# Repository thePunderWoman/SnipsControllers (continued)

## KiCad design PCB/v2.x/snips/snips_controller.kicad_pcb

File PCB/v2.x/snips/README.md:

# Snips Controller PCB (V2)

A wireless handheld controller for R2-D2 droid operation, designed for use at public events and conventions. Communicates with the droid over Zigbee, in a packetized state-report architecture.

The electrical design is in [Stackup KDL](stackup/board.kdl), using the pinned
Stackup library. The existing [KiCad PCB](snips_controller.kicad_pcb) is linked
through `snips_controller.stackup_sch`; sync it with the Stackup KiCad plugin. Run
`stackup check PCB/v2.x/snips/stackup/board.kdl` from the repository root before syncing.

A STEP model of the assembled board is in [`step/v2.0/snips_controller.step`](step/v2.0/snips_controller.step).

## V2 board

70 x 30 mm, 4 layers: F.Cu signals, In1 solid 3V3, In2 solid GND, B.Cu signals. 1.6 mm thick. Routed, not yet fabricated.

- **Module:** an ESP32-S3-MINI-1U-N8 on the top, between the macro buttons and USB, turned 270 degrees. The 19.2 mm WROOM-1U does not fit the 17.5 mm there. The turn puts the pinless GND edge on the side and the signal pins toward the stick, the OLED and the carrier; pins are assigned by position, as `GPIO_table.md` explains. USB runs about 15 mm as a result, which is well within full-speed limits. Bluetooth and ESP-NOW work with no other radio.
- **XBee:** optional. U_XBEE1 is a row of 12 hand-solder pads on the bottom for a 22 x 17 mm castellated daughter board, which carries the XBee 3 Micro, its decoupling, the RESET pull-up and RC, and the ATTN/BOOTMODE pull-up. The link is UART with flow control, not SPI. RTS and DTR also allow XBee serial firmware recovery through the ESP32. Leave the area inside the pads free of parts; vias there stay tented. See `GPIO_table.md`.
- **Reflow:** the bottom side goes first and the top side last, because Espressif requires a single reflow for the module (datasheet section 12.3). The XBee reflows on its own carrier and never goes upside down, which is what stopped the two modules from sharing this board before.
- **Radio link:** Amidala's droids use XBee Zigbee 3.0, so a Zigbee controller needs the carrier. The firmware still has to move from the XBee's SPI interface to UART, and needs a V2 pin map.
- **Programming:** USB, through the module's native USB. To force download mode, hold SW_BOOT1 while pressing the power button. RXD0's pull-up holds the latch with no firmware, so a blank board flashes after a 1 s press, with no button held during the upload.
- **No reset button:** the power button turns the board on, and only firmware turns it off. PWR_HOLD is on RXD0, whose pull-up holds the latch through any reset or USB upload, so a blank or hung board stays on until USB and the battery are removed. Keep a watchdog running to recover from a hang. C_LATCH_FB1 gives the latch hysteresis, so that pull-up cannot restart the board at power-off, and R_PWR_EN_PD1 is 22 kΩ so a rising gate cannot couple through it and lift EN.
- **Buttons:** all 13 connect directly to module GPIOs. See `GPIO_table.md`.
- **Power blocks:** the buck, charger and power latch follow V1's relative placement, all on the bottom. Two charger GND vias were moved 0.1-0.75 mm in V1's layout to clear earlier button positions. C_BUCK_IN1 turned 90 degrees with its VSYS pad straight above the VIN pin. BUCK_FB runs around the input cap and hops to F.Cu past the inductor, so both planes shield it; keep it out from under L_BUCK1. The latch is too long to fit whole, so it is split at `PWR_BTN_TRIGGER`: the switch and `PWR_LATCH_G` node sit under the stick, turned 270 degrees, and the inverter sits beside the stick's lower pins. See `diagrams/` for why they are arranged this way.
- **OLED cable:** U_OLED1's opening faces USB, and a Qwiic plug is 7.0 mm wide with its protrusions, so keep top-side parts out of x 0.9-7.9 mm from the mouth at y 52.7 mm down to the MH3 post. Check that a real cable goes in before committing the shell.
- **BOM:** the Value column carries each part's full details, including a capacitor's rated voltage, because fabs read it and the BOM has no voltage column. Keep rail names out of designators: PCBWay queried the V1.2 caps named C_3V3_* as 3.3 V parts, so V2 uses C_MCU_*.
- **Hall sensor:** U_HALL1 is on the bottom at (6.5, 4.75) mm, rotated 180 degrees, forward and left of the stick, 7.8 mm from its nearest pot pin in plan view against about 15.4 mm on V1. A 2 x 2 mm N52 magnet swings up to sit directly under the package centre. Keep at least 1.8 mm from the top of the package to the magnet at full press, or the output clips at the sensor's ±44 mT range. The stick reading against trigger travel still needs a bench test.
- **Mounting:** four Ø2.2 mm unplated holes, MH1-4, at (2.5, 2.6), (27.4, 2.8), (3, 62.5) and (27, 67) from the top-left corner, for M2 self-tapping screws into shell posts. MH3 sits above the power button, which holds the true corner, so a Ø4 post clears `C_DBNC1` by only about 0.15 mm. The carrier has a long shallow chamfer at that corner, which also clears a Ø4 post on the bottom.
- **Battery:** BT1 is a 2-pin JST PH, the common connector on pouch cells this size: pin 1 VBAT, pin 2 GND. R_TS1 ties the charger's TS pin to a fixed 10 kΩ, so there is no pack temperature monitoring. Check the polarity of the cell's lead before plugging it in.
- **USB and status LED:** J_USB1 sits 2 mm right of centre, with its CC resistors and TVS moved with it. D_RGB1 sits between SW_PWR1 and J_USB1, turned 90 degrees.
- **Through-board parts:** the Alps pegs, stick pins, USB stakes and BT1 pins all reach the other side.

## GPIO Assignment

See [`GPIO_table.md`](GPIO_table.md) for every module pin.

## Hardware Overview

| Component | Part | Notes | Layout diagram |
|---|---|---|---|
| MCU and radio | Espressif ESP32-S3-MINI-1U-N8 | Wi-Fi, Bluetooth LE and ESP-NOW, 8 MB flash, 15.4 x 15.4 x 2.4 mm, external antenna | — |
| XBee (optional) | Digi XB3-24Z8UM on a castellated carrier | Zigbee 3.0, +19 dBm, U.FL. Hand-soldered to the underside | — |
| Display | SSD1306 1.3" OLED | 128x64, monochrome, I2C | — |
| Hall trigger | DRV5055A2QDBZR (SOT-23) | Ratiometric linear hall effect, 3.3V. On the bottom of the board under the trigger magnet; senses the field perpendicular to the board. Trigger calibration accepts either magnet polarity | — |
| Thumbstick | GuliKit hall effect module | Native 3.3V, analog X/Y + click | — |
| Macro and boot buttons | Alps SKRPABE010 | 4.2 x 3.2 x 2.5 mm SMD tact switch, 1.57 N, 0.2 mm travel, 100,000 cycles. Footprint checked against the Alps land drawing | — |
| RGB LED | SK6812MINI-HS | Status indicator; specified supply begins at 3.7 V, but board supplies 3.3 V | — |
| Charger | bq25185 | USB/DC input, power path, 4.2V/500mA | [diagram](diagrams/power_charger_layout.md) |
| Buck | TLV62569 | 3.3V output, 2A | [diagram](diagrams/power_buck_layout.md) |
| Battery | Single-cell pouch, 2-pin JST PH | Cell not chosen yet. Set R_ISET1 for it; 604 Ω charges at about 500 mA | — |
| Power switch | AO3401A + AO3400A | Soft latch, hybrid hardware+firmware | [diagram](diagrams/power_control_layout.md) |

## Layout Diagrams

Suggested top-copper floorplans for the three sheets with real layout
stakes — a switching regulator, a linear charger with a thermal pad, and
the soft latch that switches the buck's enable. Each is checked
against the actual component datasheet, not just the schematic. See
[`diagrams/README.md`](diagrams/README.md) for the full list and how the
files are organized.

- [Buck converter](diagrams/power_buck_layout.md) — `/Power_Buck/*` nets in Stackup
- [Charger](diagrams/power_charger_layout.md) — `/Power_Charger/*` nets in Stackup
- [Power latch](diagrams/power_control_layout.md) — `/Power_Control/*` nets in Stackup

## Passives & Support Components

### Decoupling Caps
| Component | Value | Notes |
|---|---|---|
| DRV5055 VCC | 100nF ceramic | |
| GuliKit VCC | 100nF ceramic | |
| SK6812 VCC | 100nF ceramic | Close to supply pin |
| ICM-42670-P | 100nF + 2.2µF on VDD, 10nF on VDDIO | Close to their pins |
| OLED connector | 1µF + 100nF ceramic | |
| bq25185 VIN | 10µF + 100nF ceramic | |
| bq25185 SYS | 10µF + 100nF ceramic | |
| bq25185 BAT | 10µF ceramic | |
| TLV62569 VIN | 10µF ceramic | |
| TLV62569 VOUT | 22µF ceramic | As on V1. TI specifies 10-47 µF |
| ESP32-S3-MINI-1U 3V3 | 10µF + 100nF + 39pF ceramic | As on V1 |
| ESP32-S3-MINI-1U EN | 1µF ceramic | With R_EN_PU1, per Espressif |
| XBee VCC | 10µF + 1µF + 47pF ceramic | On the carrier, per Digi 90001543 p.52 |

### Resistors
| Signal | Value | Notes |
|---|---|---|
| bq25185 STAT1/STAT2 | 10kΩ | Open drain, pulled up to 3V3 |
| bq25185 TS/MR | 10kΩ to GND | Required with no thermistor: floating means no charging |
| I2C SDA/SCL | 4.7kΩ | So the IMU works with no OLED attached |
| Boot button | 10kΩ to 3V3 | R_BOOT_PU1 |
| ESP32 EN | 10kΩ to 3V3 | R_EN_PU1 |
| USB D+/D- | 27Ω series | R_USB_DP1 and R_USB_DM1, as on V1 |
| Trigger output | 1kΩ + 100nF | R_TRIG1 and C_TRIG1, about 1.6 kHz. The DRV5055 must not see a capacitor without a resistor |
| SK6812 DIN | 470Ω | R_RGB1 |

### Buttons
No external parts. Every button wires to GND and a module GPIO, using the internal pull-ups; see [`GPIO_table.md`](GPIO_table.md).

---

## Communication Architecture

The droids use XBee Zigbee 3.0, so the controller joins that network through the XBee on the carrier, over UART in API mode. Each droid has its own coordinator and PAN ID, and all coordinators share one AES key. Without the carrier the ESP32 can use Bluetooth or ESP-NOW.

---

## Bringup Sequence

Recommended bringup order:
1. Current-limited supply on VSYS, with no carrier fitted: press power for 1 s, then check 3V3 and idle current.
2. Flash over USB with no button held, with SW_BOOT1 held at power-on if the chip does not enumerate. Confirm `PWR_HOLD` reads high.
3. Time the shortest press that stays on, at 3.3 V and 4.2 V. The simulation gives under 0.4 s at worst, so a 1 s press is well clear. Run a USB upload with no button held, then confirm a watchdog reset reboots the board. Power off at least 20 times, on USB and on battery, and scope `PWR_EN` and `PWR_LATCH_G`: the board must stay off every time, since the simulation's margin has not been measured.
4. OLED and ICM-42670-P on I2C.
5. SK6812 RGB LED.
6. Buttons, using the pin table.
7. Charge status on STAT1 and STAT2, and VSYS sense.
8. DRV5055 and thumbstick on the ADC. Sweep the stick and the trigger together to measure how much each moves the other.
9. Solder the carrier on. Check UART traffic, CTS, SLEEP_RQ and ON/SLEEP, then XBee reset, then join a droid's network.

---

## Power Architecture

- Battery → bq25185 (charger and power path, 4.2V, 500mA) → TLV62569 (3.3V buck) → 3V3 for everything, including the carrier.
- Power switch: soft latch (AO3401A PFET + AO3400A NFET) controls the TLV62569 EN pin. USB does not hold it on.
- Boot: press the power button for about a second → latch enables 3V3 → RXD0's pull-up holds the latch through D_OR2 as soon as the chip has power → firmware drives RXD0 high.
- Shutdown: firmware sees a hold on IO21 → graceful shutdown → RXD0 low → the gate decays through R_LATCH_G1 → C_LATCH_FB1 kicks it clear of threshold as PWR_EN falls → power cut after about 0.8-2.6 s, counted from release if the button is still held.
- bq25185 STAT1 and STAT2 go to IO15 and IO14 (open drain, 10kΩ pull-ups to 3V3).
- Battery voltage: VSYS through R_VSYS1/R_VSYS2 to IO7, reading VSYS/3.
- Below about 3.3 V on the battery the buck passes it through, and the DRV5055's minimum is 3.0 V, so the firmware cutoff should sit above that.

## Power Management

Firmware implements tiered power saving:
- **Active**: full brightness OLED, normal polling rate
- **Idle (short timeout)**: OLED dimmed via SSD1306 contrast command
- **Idle (long timeout)**: OLED off
- **Sleep**: MCU sleep, wake on any button press via GPIO interrupt

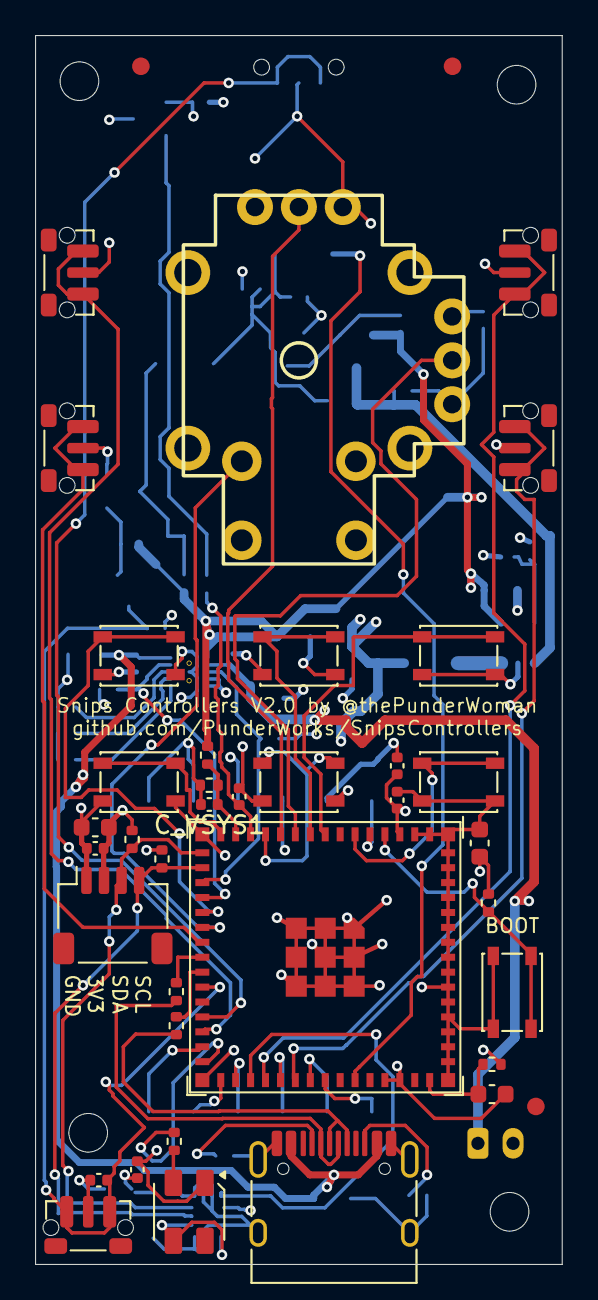
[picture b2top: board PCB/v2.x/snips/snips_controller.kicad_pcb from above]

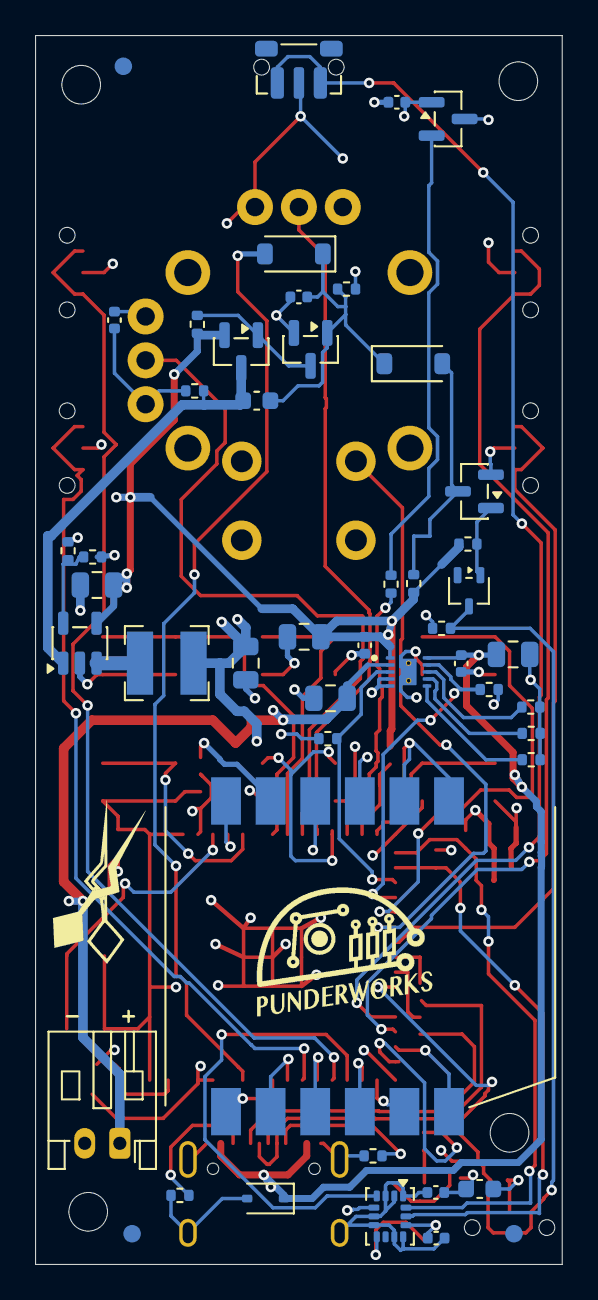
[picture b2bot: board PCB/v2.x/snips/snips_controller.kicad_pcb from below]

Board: 4 copper layers, 30.0 x 70.0 mm, 93 parts (50 on the bottom side), 56 nets.

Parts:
BT1: JST PH 2-pin 2mm | S2B-PH-K(LF)(SN) | JST | Throu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; JST_PH_S2B-PH-K_1x02_P2.00mm_Horizontal
C_BAT1: 10µF 25V X5R ±10% | CL21A106KAYNNNE | Samsung | 0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; C_0805_2012Metric
C_BUCK_IN1: 10µF 25V X5R ±10% | CL21A106KAYNNNE | Samsung | 0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; C_0805_2012Metric
C_BUCK_OUT1: 22µF 25V X5R ±20% | CL21A226MAQNNNE | Samsung | 0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; C_0805_2012Metric
C_DBNC1: 100nF 16V X7R ±10% | CL05B104KO5NNNC | Samsung | 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; C_0402_1005Metric
C_EN1: 1µF 50V X5R ±10% | CL10A105KB8NNNC | Samsung | 06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; C_0603_1608Metric
C_HALL1: 100nF 16V X7R ±10% | CL05B104KO5NNNC | Samsung | 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; C_0402_1005Metric
C_IMU_1: 100nF 16V X7R ±10% | CL05B104KO5NNNC | Samsung | 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; C_0402_1005Metric
C_IMU_2: 2.2µF 10V X7R ±10% | CL10B225KP8NNNC | Samsung | 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; C_0603_1608Metric
C_IMU_3: 10nF 50V X7R ±10% | CL05B103KB5NNNC | Samsung | 0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; C_0402_1005Metric
C_LATCH_FB1: 1µF 50V X5R ±10% | CL10A105KB8NNNC | Samsung | 06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; C_0603_1608Metric
C_LATCH_G1: 1µF 6.3V X5R ±10% | CL05A105KQ5NNNC | Samsung | 0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; C_0402_1005Metric
C_MCU_1: 10µF 10V X5R ±10% | CL10A106KP8NNNC | Samsung | 0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; C_0603_1608Metric
C_MCU_2: 100nF 16V X7R ±10% | CL05B104KO5NNNC | Samsung | 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; C_0402_1005Metric
C_MCU_3: 39pF 50V NP0 ±5% | CC0402JRNPO9BN390 | Yageo | 04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; C_0402_1005Metric
C_OLED_1: 1µF 50V X5R ±10% | CL10A105KB8NNNC | Samsung | 06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; C_0603_1608Metric
C_OLED_2: 100nF 16V X7R ±10% | CL05B104KO5NNNC | Samsung | 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; C_0402_1005Metric
C_RGB1: 100nF 16V X7R ±10% | CL05B104KO5NNNC | Samsung | 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; C_0402_1005Metric
C_STICK1: 100nF 16V X7R ±10% | CL05B104KO5NNNC | Samsung | 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; C_0402_1005Metric
C_SYS_1: 10µF 25V X5R ±10% | CL21A106KAYNNNE | Samsung | 0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; C_0805_2012Metric
C_SYS_2: 100nF 16V X7R ±10% | CL05B104KO5NNNC | Samsung | 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; C_0402_1005Metric
C_TRIG1: 100nF 16V X7R ±10% | CL05B104KO5NNNC | Samsung | 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; C_0402_1005Metric
C_VIN_1: 10µF 25V X5R ±10% | CL21A106KAYNNNE | Samsung | 0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; C_0805_2012Metric
C_VIN_2: 100nF 16V X7R ±10% | CL05B104KO5NNNC | Samsung | 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; C_0402_1005Metric
C_VSYS1: 100nF 16V X7R ±10% | CL05B104KO5NNNC | Samsung | 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; C_0402_1005Metric
D_INV_ISO1: Schottky diode 30V 200mA | BAT54W-7-F | Diodes In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; SOT-323_SC-70
D_OR1, D_OR2: 1N4148W switching diode 75V 150mA | 1N4148W | ST 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; D_SOD-123
D_RGB1: Addressable RGB LED | SK6812MINI-HS | OPSCO | 3.5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; SK6812MINI-HS-012
D_VBUS_TVS1: TVS diode 5V bidirectional | TPPESD5V0S1BA | TECH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; D_SOD-323
FID1, FID2, FID3, FID4, FID5, FID6: Fiducial_1mm_Mask2mm
J_STICK1: Hall thumbstick | GuliKit_Thumbstick | GuliKit | 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; GuliKit_HallStick
J_USB1: USB-C receptacle 16-pin | TYPE-C-31-M-12 | Hropar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; USB_C_Receptacle_HRO_TYPE-C-31-M-12
LOGO2: LOGO
LOGO4: PunderWorks_Logo_10mm
L_BUCK1: 2.2µH ±20% 2.9A 44mΩ power inductor | SRN4018-2R2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; L_Bourns-SRN4018
MH1, MH2, MH3, MH4: MountingHole_2.2mm_M2_ISO14580
Q_INV1: NPN transistor 40V 200mA hFE 100-300 | MMBT3904(R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; SOT-23
Q_LATCH1: N-channel MOSFET 30V 5.7A | AO3400A | AOS | SOT-23; SOT-23
Q_PWR1: P-channel MOSFET 30V 4A | AO3401A | AOS | SOT-23; SOT-23
R_BOOT_PU1: 10kΩ ±1% 62.5mW | 0402WGF1002TCE | UNI-ROYAL | 04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; R_0402_1005Metric
R_BTN_PU1: 100kΩ ±1% 62.5mW | 0402WGF1003TCE | UNI-ROYAL | 0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; R_0402_1005Metric
R_CC1, R_CC2: 5.1kΩ ±1% 62.5mW | 0402WGF5101TCE | UNI-ROYAL | 0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; R_0402_1005Metric
R_EN_PU1: 10kΩ ±1% 62.5mW | 0402WGF1002TCE | UNI-ROYAL | 04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; R_0402_1005Metric
R_FB1: 255kΩ ±1% 62.5mW | RC0402FR-07255KL | Yageo | 0402; R_0402_1005Metric
R_FB2: 56.2kΩ ±1% 62.5mW | RC0402FR-0756K2L | Yageo | 04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; R_0402_1005Metric
R_GATE1: 100kΩ ±1% 62.5mW | 0402WGF1003TCE | UNI-ROYAL | 0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; R_0402_1005Metric
R_I2C_SCL1, R_I2C_SDA1: 4.7kΩ ±1% 62.5mW | 0402WGF4701TCE | UNI-ROYAL | 0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; R_0402_1005Metric
R_INV_BASE1: 220kΩ ±1% 62.5mW | 0402WGF2203TCE | UNI-ROYAL | 0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; R_0402_1005Metric
R_INV_PU1: 220kΩ ±1% 62.5mW | 0402WGF2203TCE | UNI-ROYAL | 0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; R_0402_1005Metric
R_ISET1: 604Ω ±1% 62.5mW | AC0402FR-07604RL | Yageo | 0402; R_0402_1005Metric
R_LATCH_G1: 1MΩ ±1% 62.5mW | 0402WGF1004TCE | UNI-ROYAL | 0402; R_0402_1005Metric
R_PWR_EN_PD1: 22kΩ ±1% 62.5mW | 0402WGF2202TCE | UNI-ROYAL | 04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; R_0402_1005Metric
R_RGB1: 470Ω ±1% 62.5mW | 0402WGF4700TCE | UNI-ROYAL | 04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; R_0402_1005Metric
R_STAT1, R_STAT2: 10kΩ ±1% 62.5mW | 0402WGF1002TCE | UNI-ROYAL | 04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; R_0402_1005Metric
R_TRIG1: 1kΩ ±1% 62.5mW | 0402WGF1001TCE | UNI-ROYAL | 0402; R_0402_1005Metric
R_TS1: 10kΩ ±1% 62.5mW | 0402WGF1002TCE | UNI-ROYAL | 04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; R_0402_1005Metric
R_USB_DM1: 27Ω ±1% 62.5mW | RC0402FR-0727RL | Yageo | 0402; R_0402_1005Metric
R_USB_DP1: 27Ω ±1% 62.5mW | RC0402FR-0727RL | Yageo | 0402; R_0402_1005Metric
R_VSET1: 18kΩ ±1% 62.5mW | RC0402FR-0718KL | Yageo | 0402; R_0402_1005Metric
R_VSYS1: 200kΩ ±1% 62.5mW | 0402WGF2003TCE | UNI-ROYAL | 0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; R_0402_1005Metric
R_VSYS2: 100kΩ ±1% 62.5mW | 0402WGF1003TCE | UNI-ROYAL | 0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; R_0402_1005Metric
SW_BOOT1: Tact switch 1.6N 100k cycles | SKRPABE010 | Alps 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; SW_Alps_SKRP
SW_MACRO1, SW_MACRO2, SW_MACRO3, SW_MACRO4, SW_MACRO5, SW_MACRO6: Tact switch 1.6N 100k cycles | SKRPABE010 | Alps 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; SW_Alps_SKRP
SW_PWR1: Side-push tact switch 1.6N 100k cycles | SKRTLAE0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; SW_Push_1P1T-MP_NO_Horizontal_Alps_SKRTLAE010
SW_THR_DN1: Side-push tact switch 1.6N 100k cycles | SKRTLAE0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; SW_Push_1P1T-MP_NO_Horizontal_Alps_SKRTLAE010
SW_THR_UP1: Side-push tact switch 1.6N 100k cycles | SKRTLAE0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; SW_Push_1P1T-MP_NO_Horizontal_Alps_SKRTLAE010
SW_TRIG_DIG1: Side-push tact switch 1.6N 100k cycles | SKRTLAE0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; SW_Push_1P1T-MP_NO_Horizontal_Alps_SKRTLAE010
SW_VOL_DN1: Side-push tact switch 1.6N 100k cycles | SKRTLAE0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; SW_Push_1P1T-MP_NO_Horizontal_Alps_SKRTLAE010
SW_VOL_UP1: Side-push tact switch 1.6N 100k cycles | SKRTLAE0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; SW_Push_1P1T-MP_NO_Horizontal_Alps_SKRTLAE010
U_BUCK1: Adjustable buck converter 2A | TLV62569DBVR | TI 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; SOT-23-5
U_CHG1: 1-cell Li-ion charger 1A | BQ25185DLHR | TI | WSO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; IC_BQ25185DLHR
U_HALL1: Linear hall sensor A2 ±42mT | DRV5055A2QDBZR | TI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; SOT-23
U_IMU1: 6-axis IMU | ICM-42670-P | TDK InvenSense | LGA-1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; LGA-14_3x2.5mm_P0.5mm_LayoutBorder3x4y
U_MCU1: Wi-Fi BLE module 8MB flash no PSRAM | ESP32-S3-MI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; ESP32-S3-MINI-1U
U_OLED1: JST SH 4-pin 1mm Qwiic | SM04B-SRSS-TB(LF)(SN) | 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; JST_SH_SM04B-SRSS-TB_1x04-1MP_P1.00mm_Horizontal
U_XBEE1: XBee carrier pads no part | Snips XBee carrier | 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; XBee_Carrier_Castellated

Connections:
3V3: C_BUCK_OUT1.1, C_HALL1.1, C_IMU_1.1, C_IMU_2.1, C_IMU_3.1, C_MCU_1.1, C_MCU_2.1, C_MCU_3.1, C_OLED_1.1, C_OLED_2.1, C_RGB1.1, C_STICK1.1, D_RGB1.3, J_STICK1.3 (X_HI), J_STICK1.3' (Y_HI), L_BUCK1.2, R_BOOT_PU1.2, R_BTN_PU1.1, R_EN_PU1.2, R_FB1.2, R_I2C_SCL1.1, R_I2C_SDA1.1, R_STAT1.2, R_STAT2.2, U_HALL1.1, U_IMU1.5, U_IMU1.8, U_IMU1.12, U_MCU1.3, U_OLED1.2 (VCC), U_XBEE1.9, U_XBEE1.10
/Accelerometer/I2C_SCL: R_I2C_SCL1.2, U_IMU1.13, U_MCU1.17, U_OLED1.4 (SCL)
/Accelerometer/I2C_SDA: R_I2C_SDA1.2, U_IMU1.14, U_MCU1.16, U_OLED1.3 (SDA)
/Buttons_Direct/BTN_MACRO1: SW_MACRO1.1, U_MCU1.20
/Buttons_Direct/BTN_MACRO2: SW_MACRO2.1, U_MCU1.9
/Buttons_Direct/BTN_MACRO3: SW_MACRO3.1, U_MCU1.8
/Buttons_Direct/BTN_MACRO4: SW_MACRO4.1, U_MCU1.15
/Buttons_Direct/BTN_MACRO5: SW_MACRO5.1, U_MCU1.12
/Buttons_Direct/BTN_MACRO6: SW_MACRO6.1, U_MCU1.6
/Buttons_Direct/BTN_THR_DN: SW_THR_DN1.1, U_MCU1.22
/Buttons_Direct/BTN_THR_UP: SW_THR_UP1.1, U_MCU1.28
/Buttons_Direct/BTN_TRIG_DIG: SW_TRIG_DIG1.1, U_MCU1.27
/Buttons_Direct/BTN_VOL_DN: SW_VOL_DN1.1, U_MCU1.36
/Buttons_Direct/BTN_VOL_UP: SW_VOL_UP1.1, U_MCU1.34
/Hall_Trigger/TRIG_ADC: C_TRIG1.1, R_TRIG1.2, U_MCU1.13
/Hall_Trigger/TRIG_ANALOG: R_TRIG1.1, U_HALL1.2
/MCU_Core/BTN_STICK: J_STICK1.a (SW_A), U_MCU1.21
/MCU_Core/MCU_BOOT: R_BOOT_PU1.1, SW_BOOT1.2, U_MCU1.4
/MCU_Core/MCU_EN: C_EN1.1, R_EN_PU1.1, U_MCU1.45
/MCU_Core/PWR_BTN_SENSE: C_DBNC1.1, D_INV_ISO1.3 (K), R_BTN_PU1.2, SW_PWR1.1, U_MCU1.25
/MCU_Core/PWR_HOLD: D_OR2.2 (A), U_MCU1.40
/MCU_Core/RGB_DIN: R_RGB1.2, U_MCU1.30
/MCU_Core/STAT1: R_STAT1.1, U_CHG1.9 (STAT1), U_MCU1.19
/MCU_Core/STAT2: R_STAT2.1, U_CHG1.3 (STAT2), U_MCU1.18
/MCU_Core/STICK_X: J_STICK1.2 (X_OUT), U_MCU1.11
/MCU_Core/STICK_Y: J_STICK1.2' (Y_OUT), U_MCU1.10
/MCU_Core/USB_DM: J_USB1.A7 (D-), J_USB1.B7 (D-), R_USB_DM1.1
/MCU_Core/USB_DM_MCU: R_USB_DM1.2, U_MCU1.23
/MCU_Core/USB_DP: J_USB1.A6 (D+), J_USB1.B6 (D+), R_USB_DP1.1
/MCU_Core/USB_DP_MCU: R_USB_DP1.2, U_MCU1.24
/MCU_Core/VSYS_SENSE: C_VSYS1.1, R_VSYS1.2, R_VSYS2.1, U_MCU1.14
/Power_Buck/BUCK_FB: R_FB1.1, R_FB2.1, U_BUCK1.5 (FB)
/Power_Buck/BUCK_SW: L_BUCK1.1, U_BUCK1.3 (SW)
/Power_Buck/PWR_EN: C_LATCH_FB1.1, Q_PWR1.3 (D), R_PWR_EN_PD1.1, U_BUCK1.1 (EN)
/Power_Charger/CHG_ISET: R_ISET1.1, U_CHG1.8 (ISET)
/Power_Charger/CHG_TS: R_TS1.1, U_CHG1.6 (TS/MR)
/Power_Charger/CHG_VSET: R_VSET1.1, U_CHG1.7 (ILIM/VSET)
/Power_Control/PWR_BTN_INV_BASE: D_INV_ISO1.1 (A), Q_INV1.1 (B), R_INV_BASE1.2
/Power_Control/PWR_BTN_TRIGGER: D_OR1.2 (A), Q_INV1.3 (C), R_INV_PU1.2
/Power_Control/PWR_GATE: Q_LATCH1.3 (D), Q_PWR1.1 (G), R_GATE1.2
/Power_Control/PWR_LATCH_G: C_LATCH_FB1.2, C_LATCH_G1.2, D_OR1.1 (K), D_OR2.1 (K), Q_LATCH1.1 (G), R_LATCH_G1.2
/RGB_LED/RGB_DIN_R: D_RGB1.2, R_RGB1.1
/USB_C/USB_CC1: J_USB1.A5 (CC1), R_CC1.1
/USB_C/USB_CC2: J_USB1.B5 (CC2), R_CC2.1
/XBee/XBEE_CTS: U_MCU1.29, U_XBEE1.1
/XBee/XBEE_DIN: U_MCU1.31, U_XBEE1.2
/XBee/XBEE_DOUT: U_MCU1.32, U_XBEE1.3
/XBee/XBEE_ON_SLEEP: U_MCU1.37, U_XBEE1.5
/XBee/XBEE_RESET: U_MCU1.38, U_XBEE1.6
/XBee/XBEE_RTS: U_MCU1.35, U_XBEE1.4
/XBee/XBEE_SLEEP_RQ: U_MCU1.5, U_XBEE1.7
ACCEL_INT1: U_IMU1.4, U_MCU1.33
GND: BT1.2, C_BAT1.2, C_BUCK_IN1.2, C_BUCK_OUT1.2, C_DBNC1.2, C_EN1.2, C_HALL1.2, C_IMU_1.2, C_IMU_2.2, C_IMU_3.2, C_LATCH_G1.1, C_MCU_1.2, C_MCU_2.2, C_MCU_3.2, C_OLED_1.2, C_OLED_2.2, C_RGB1.2, C_STICK1.2, C_SYS_1.2, C_SYS_2.2, C_TRIG1.2, C_VIN_1.2, C_VIN_2.2, C_VSYS1.2, D_RGB1.1, D_VBUS_TVS1.2 (A2), J_STICK1.1 (X_LO), J_STICK1.1' (Y_LO), J_STICK1.c (SW_C), J_USB1.A1 (GND), J_USB1.A12 (GND), J_USB1.B1 (GND), J_USB1.B12 (GND), J_USB1.SH (SHIELD), Q_INV1.2 (E), Q_LATCH1.2 (S), R_CC1.2, R_CC2.2, R_FB2.2, R_ISET1.2, R_LATCH_G1.1, R_PWR_EN_PD1.2, R_TS1.2, R_VSET1.2, R_VSYS2.2, SW_BOOT1.1, SW_MACRO1.2, SW_MACRO2.2, SW_MACRO3.2, SW_MACRO4.2, SW_MACRO5.2, SW_MACRO6.2, SW_PWR1.2, SW_THR_DN1.2, SW_THR_UP1.2, SW_TRIG_DIG1.2, SW_VOL_DN1.2, SW_VOL_UP1.2, U_BUCK1.2 (GND), U_CHG1.4 (~CE), U_CHG1.5 (GND), U_CHG1.11 (THERMAL_PAD), U_CHG1.12, U_CHG1.13, U_HALL1.3, U_IMU1.1, U_IMU1.2, U_IMU1.3, U_IMU1.6, U_IMU1.7, U_IMU1.10, U_IMU1.11, U_MCU1.1, U_MCU1.2, U_MCU1.42, U_MCU1.43, U_MCU1.46, U_MCU1.47, U_MCU1.48, U_MCU1.49, U_MCU1.50, U_MCU1.51, U_MCU1.52, U_MCU1.53, U_MCU1.54, U_MCU1.55, U_MCU1.56, U_MCU1.57, U_MCU1.58, U_MCU1.59, U_MCU1.60, U_MCU1.61, U_MCU1.62, U_MCU1.63, U_MCU1.64, U_MCU1.65, U_OLED1.1 (GND), U_XBEE1.8, U_XBEE1.11, U_XBEE1.12
VBAT: BT1.1, C_BAT1.1, U_CHG1.2 (BAT)
VBUS: C_VIN_1.1, C_VIN_2.1, D_VBUS_TVS1.1 (A1), J_USB1.A4 (VBUS), J_USB1.A9 (VBUS), J_USB1.B4 (VBUS), J_USB1.B9 (VBUS), U_CHG1.10 (IN)
VSYS: C_BUCK_IN1.1, C_SYS_1.1, C_SYS_2.1, Q_PWR1.2 (S), R_GATE1.1, R_INV_BASE1.1, R_INV_PU1.1, R_VSYS1.1, U_BUCK1.4 (VIN), U_CHG1.1 (SYS)

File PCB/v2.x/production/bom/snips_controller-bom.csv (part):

Refs,Quantity,Value,Footprint,MF,MPN,LCSC,Mouser,DigiKey,Hand,DNP
"U_CHG1","1","1-cell Li-ion charger 1A | BQ25185DLHR | TI | WSON-10","BQ25185DLHR:IC_BQ25185DLHR","Texas Instruments","BQ25185DLHR","C19725033","","","",""
"R_BTN_PU1,R_GATE1,R_VSYS2","3","100kΩ ±1% 62.5mW | 0402WGF1003TCE | UNI-ROYAL | 0402","Resistor_SMD:R_0402_1005Metric","UNI-ROYAL(Uniroyal Elec)","0402WGF1003TCE","C25741","","","",""
"C_DBNC1,C_HALL1,C_IMU_1,C_MCU_2,C_OLED_2,C_RGB1,C_STICK1,C_SYS_2,C_TRIG1,C_VIN_2,C_VSYS1","11","100nF 16V X7R ±10% | CL05B104KO5NNNC | Samsung | 0402","Capacitor_SMD:C_0402_1005Metric","Samsung Electro-Mechanics","CL05B104KO5NNNC","C1525","","","",""
"R_BOOT_PU1,R_EN_PU1,R_STAT1,R_STAT2,R_TS1","5","10kΩ ±1% 62.5mW | 0402WGF1002TCE | UNI-ROYAL | 0402","Resistor_SMD:R_0402_1005Metric","UNI-ROYAL(Uniroyal Elec)","0402WGF1002TCE","C25744","","","",""
"C_IMU_3","1","10nF 50V X7R ±10% | CL05B103KB5NNNC | Samsung | 0402","Capacitor_SMD:C_0402_1005Metric","Samsung Electro-Mechanics","CL05B103KB5NNNC","C15195","","","",""
"C_MCU_1","1","10µF 10V X5R ±10% | CL10A106KP8NNNC | Samsung | 0603","Capacitor_SMD:C_0603_1608Metric","Samsung Electro-Mechanics","CL10A106KP8NNNC","C19702","","","",""
"C_BAT1,C_BUCK_IN1,C_SYS_1,C_VIN_1","4","10µF 25V X5R ±10% | CL21A106KAYNNNE | Samsung | 0805","Capacitor_SMD:C_0805_2012Metric","Samsung Electro-Mechanics","CL21A106KAYNNNE","C15850","","","",""
"R_VSET1","1","18kΩ ±1% 62.5mW | RC0402FR-0718KL | Yageo | 0402","Resistor_SMD:R_0402_1005Metric","Yageo","RC0402FR-0718KL","C138044","","","",""
"R_LATCH_G1","1","1MΩ ±1% 62.5mW | 0402WGF1004TCE | UNI-ROYAL | 0402","Resistor_SMD:R_0402_1005Metric","UNI-ROYAL(Uniroyal Elec)","0402WGF1004TCE","C26083","","","",""
"D_OR1,D_OR2","2","1N4148W switching diode 75V 150mA | 1N4148W | ST | SOD-123","Diode_SMD:D_SOD-123","ST(Semtech)","1N4148W","C81598","","","",""
"R_TRIG1","1","1kΩ ±1% 62.5mW | 0402WGF1001TCE | UNI-ROYAL | 0402","Resistor_SMD:R_0402_1005Metric","UNI-ROYAL(Uniroyal Elec)","0402WGF1001TCE","C11702","","","",""
"C_EN1,C_LATCH_FB1,C_OLED_1","3","1µF 50V X5R ±10% | CL10A105KB8NNNC | Samsung | 0603","Capacitor_SMD:C_0603_1608Metric","Samsung Electro-Mechanics","CL10A105KB8NNNC","C15849","","","",""
"C_LATCH_G1","1","1µF 6.3V X5R ±10% | CL05A105KQ5NNNC | Samsung | 0402","Capacitor_SMD:C_0402_1005Metric","Samsung Electro-Mechanics","CL05A105KQ5NNNC","C107372","","","",""
"C_IMU_2","1","2.2µF 10V X7R ±10% | CL10B225KP8NNNC | Samsung | 0603","Capacitor_SMD:C_0603_1608Metric","Samsung Electro-Mechanics","CL10B225KP8NNNC","C100082","","","",""
"L_BUCK1","1","2.2µH ±20% 2.9A 44mΩ power inductor | SRN4018-2R2M | Bourns | SMD 4x4mm","Inductor_SMD:L_Bourns-SRN4018","Bourns","SRN4018-2R2M","C913207","","","",""
"R_VSYS1","1","200kΩ ±1% 62.5mW | 0402WGF2003TCE | UNI-ROYAL | 0402","Resistor_SMD:R_0402_1005Metric","UNI-ROYAL(Uniroyal Elec)","0402WGF2003TCE","C25764","","","",""
"R_INV_BASE1,R_INV_PU1","2","220kΩ ±1% 62.5mW | 0402WGF2203TCE | UNI-ROYAL | 0402","Resistor_SMD:R_0402_1005Metric","UNI-ROYAL(Uniroyal Elec)","0402WGF2203TCE","C25767","","","",""
"R_PWR_EN_PD1","1","22kΩ ±1% 62.5mW | 0402WGF2202TCE | UNI-ROYAL | 0402","Resistor_SMD:R_0402_1005Metric","UNI-ROYAL(Uniroyal Elec)","0402WGF2202TCE","C25768","","","",""
"C_BUCK_OUT1","1","22µF 25V X5R ±20% | CL21A226MAQNNNE | Samsung | 0805","Capacitor_SMD:C_0805_2012Metric","Samsung Electro-Mechanics","CL21A226MAQNNNE","C45783","","","",""
"R_FB1","1","255kΩ ±1% 62.5mW | RC0402FR-07255KL | Yageo | 0402","Resistor_SMD:R_0402_1005Metric","Yageo","RC0402FR-07255KL","C327361","","","",""
"R_USB_DM1,R_USB_DP1","2","27Ω ±1% 62.5mW | RC0402FR-0727RL | Yageo | 0402","Resistor_SMD:R_0402_1005Metric","Yageo","RC0402FR-0727RL","C138021","","","",""
"C_MCU_3","1","39pF 50V NP0 ±5% | CC0402JRNPO9BN390 | Yageo | 0402","Capacitor_SMD:C_0402_1005Metric","Yageo","CC0402JRNPO9BN390","C106223","","","",""
"R_I2C_SCL1,R_I2C_SDA1","2","4.7kΩ ±1% 62.5mW | 0402WGF4701TCE | UNI-ROYAL | 0402","Resistor_SMD:R_0402_1005Metric","UNI-ROYAL(Uniroyal Elec)","0402WGF4701TCE","C25900","","","",""
"R_RGB1","1","470Ω ±1% 62.5mW | 0402WGF4700TCE | UNI-ROYAL | 0402","Resistor_SMD:R_0402_1005Metric","UNI-ROYAL(Uniroyal Elec)","0402WGF4700TCE","C25117","","","",""
"R_CC1,R_CC2","2","5.1kΩ ±1% 62.5mW | 0402WGF5101TCE | UNI-ROYAL | 0402","Resistor_SMD:R_0402_1005Metric","UNI-ROYAL(Uniroyal Elec)","0402WGF5101TCE","C25905","","","",""
"R_FB2","1","56.2kΩ ±1% 62.5mW | RC0402FR-0756K2L | Yageo | 0402","Resistor_SMD:R_0402_1005Metric","Yageo","RC0402FR-0756K2L","C183355","","","",""
"U_IMU1","1","6-axis IMU | ICM-42670-P | TDK InvenSense | LGA-14 2.5x3mm","Package_LGA:LGA-14_3x2.5mm_P0.5mm_LayoutBorder3x4y","TDK InvenSense","ICM-42670-P","C3288646","","","",""
"R_ISET1","1","604Ω ±1% 62.5mW | AC0402FR-07604RL | Yageo | 0402","Resistor_SMD:R_0402_1005Metric","Yageo","AC0402FR-07604RL","C227167","","","",""
"D_RGB1","1","Addressable RGB LED | SK6812MINI-HS | OPSCO | 3.5x3.5mm SMD | top-mount lens up","SnipsControllers_Custom:SK6812MINI-HS-012","OPSCO Optoelectronics","SK6812MINI-HS","C2922787","","","",""
"U_BUCK1","1","Adjustable buck converter 2A | TLV62569DBVR | TI | SOT-23-5","Package_TO_SOT_SMD:SOT-23-5","Texas Instruments","TLV62569DBVR","C141836","","","",""
"J_STICK1","1","Hall thumbstick | GuliKit_Thumbstick | GuliKit | Through-hole | DNP - hand-fitted - do not assemble","SnipsControllers_Custom:GuliKit_HallStick","GuliKit","GuliKit_Thumbstick","","","","Yes","Yes"
"BT1","1","JST PH 2-pin 2mm | S2B-PH-K(LF)(SN) | JST | Through-hole | RIGHT-ANGLE HORIZONTAL not vertical","Connector_JST:JST_PH_S2B-PH-K_1x02_P2.00mm_Horizontal","JST","S2B-PH-K(LF)(SN)","C265016","","","",""
"U_OLED1","1","JST SH 4-pin 1mm Qwiic | SM04B-SRSS-TB(LF)(SN) | JST | SMD | side entry right-angle","Connector_JST:JST_SH_SM04B-SRSS-TB_1x04-1MP_P1.00mm_Horizontal","JST","SM04B-SRSS-TB(LF)(SN)","C160404","","","",""
"U_HALL1","1","Linear hall sensor A2 ±42mT | DRV5055A2QDBZR | TI | SOT-23","Package_TO_SOT_SMD:SOT-23","Texas Instruments","DRV5055A2QDBZR","C266131","","","",""
"Q_LATCH1","1","N-channel MOSFET 30V 5.7A | AO3400A | AOS | SOT-23","Package_TO_SOT_SMD:SOT-23","Alpha & Omega Semicon","AO3400A","C20917","","","",""
"Q_INV1","1","NPN transistor 40V 200mA hFE 100-300 | MMBT3904(RANGE:100-300) | JCET | SOT-23","Package_TO_SOT_SMD:SOT-23","Jiangsu Changjing Electronics Technology Co., Ltd.","MMBT3904(RANGE:100-300)","C20526","","","",""
"Q_PWR1","1","P-channel MOSFET 30V 4A | AO3401A | AOS | SOT-23","Package_TO_SOT_SMD:SOT-23","Alpha & Omega Semicon","AO3401A","C15127","","","",""
"D_INV_ISO1","1","Schottky diode 30V 200mA | BAT54W-7-F | Diodes Inc | SOT-323","Package_TO_SOT_SMD:SOT-323_SC-70","Diodes Incorporated","BAT54W-7-F","C134417","","","",""
"SW_PWR1,SW_THR_DN1,SW_THR_UP1,SW_TRIG_DIG1,SW_VOL_DN1,SW_VOL_UP1","6","Side-push tact switch 1.6N 100k cycles | SKRTLAE010 | Alps | SMD 4.5x3.4x3.3mm | right-angle","Button_Switch_SMD:SW_Push_1P1T-MP_NO_Horizontal_Alps_SKRTLAE010","Alps Alpine","SKRTLAE010","C110293","","","",""
"D_VBUS_TVS1","1","TVS diode 5V bidirectional | TPPESD5V0S1BA | TECH PUBLIC | SOD-323","Diode_SMD:D_SOD-323","TECH PUBLIC","TPPESD5V0S1BA","C587144","","","",""
"SW_BOOT1,SW_MACRO1,SW_MACRO2,SW_MACRO3,SW_MACRO4,SW_MACRO5,SW_MACRO6","7","Tact switch 1.6N 100k cycles | SKRPABE010 | Alps | SMD 4.2x3.2x2.5mm | top actuated","SnipsControllers_Custom:SW_Alps_SKRP","Alps Alpine","SKRPABE010","C115360","","","",""
"J_USB1","1","USB-C receptacle 16-pin | TYPE-C-31-M-12 | Hroparts Elec | SMD with through-hole shell tabs | right-angle","Connector_USB:USB_C_Receptacle_HRO_TYPE-C-31-M-12","Hroparts Elec","TYPE-C-31-M-12","C165948","","","",""
"U_MCU1","1","Wi-Fi BLE module 8MB flash no PSRAM | ESP32-S3-MINI-1U-N8 | Espressif | SMD module 15.4x15.4mm | N8 variant with external antenna connector","Espressif:ESP32-S3-MINI-1U","Espressif Systems","ESP32-S3-MINI-1U-N8","C2980299","","","",""
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
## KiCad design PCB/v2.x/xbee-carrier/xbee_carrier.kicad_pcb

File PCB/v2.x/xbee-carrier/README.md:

# Snips XBee carrier

A 2-layer castellated daughter board that puts a Digi XBee 3 PRO Micro on the V2 controller's underside. It is optional, and V2 runs without it. The mating footprint on V2 is `U_XBEE1`, `XBee_Carrier_Castellated`.

A STEP model of the assembled board is in [`step/xbee_carrier.step`](step/xbee_carrier.step).

## Board

- **Size:** 22 x 17 mm, 0.8 mm thick, 2 layers. The chamfer clears the MH3 shell post on V2.
- **Orientation:** the XBee side faces away from V2 and the bottom sits flat on V2's underside. This board's top view matches V2's footprint coordinates directly, and the chamfer shows which way round it goes.
- **Height below V2:** about 3.2 mm with the module, plus the U.FL plug.
- **Edge:** 12 plated half holes at 2.54 mm pitch. Order as castellated holes, with a finish that wets well, such as ENIG.
- **Clearance:** the board uses 0.15 mm in the corridors between the module's pad tips and the castellations (`xbee_carrier.kicad_dru`).

## Assembly

- Reflow on the top side only. The module is MSL 3, so follow Digi's handling rules.
- Check that nothing is left proud on the bottom. It has no parts, and V2's vias under it are tented.
- Solder the carrier to V2 by hand, through the 1.7 mm of V2 land that extends past each castellation.

## Electrical

| Part | Value | Purpose |
|---|---|---|
| C_XB_47P1, C_XB_1U1 | 47 pF, 1 µF | At pad 2, per Digi 90001543 p.52. 25 V part for the 1 µF, so it keeps its value at 3.3 V |
| C_XB_10U1 | 10 µF 0402 | Digi's recommended bulk cap. About 4 µF at 3.3 V, and V2's rail is close by |
| R_XB_RST_PU1, C_XB_RST1, R_XB_RST1 | 10 kΩ, 100 nF, 100 Ω | V2 drives RESET open drain, so the pull-up is here. About 1 ms of reset as the rail rises |
| R_XB_ATTN_PU1 | 10 kΩ | BOOTMODE shares this pin and must not be low at reset |

Pads 1-6 are CTS, DIN, DOUT, RTS, ON/SLEEP and RESET. Pad 7 is SLEEP_RQ, 8 GND, 9-10 3V3, and 11-12 GND. Names match V2's nets.

## Layout rules

- No top-side copper under the module, and no copper or vias at its three RF test points (Digi 90001543 p.58). The `XB3-24Z8UM` footprint carries both as rule areas. Signals cross under the module on the bottom layer. The top-side rule stops 0.5 mm short of the module's edge, so pads can reach their vias.
- Test point positions come from the bottom view on p.34, since the manual has no Micro keepout drawing.
- The 3D model is Digi's `XB3-UFL-MMT.STEP`.

## Checks

```
stackup check PCB/v2.x/xbee-carrier/stackup/board.kdl
```

CI checks the design, the BOM and the PCB sync. Sync with the Stackup KiCad plugin after any KDL change.

## Production

Files are in `production/`, built from this board: `jlcpcb/` holds the order set as `Snips_XBee_Carrier_1_0.zip` with its BOM and positions, and `gerbers/`, `placement/` and `bom/` hold the separate exports. Regenerate them after any board change.

When ordering:

- Select castellated holes. The job file marks the board as castellated, and there are 12 half holes on the two long edges.
- Use 0.8 mm thickness and ENIG. The board file's copper finish is unset, so choose this in the order.
- The XBee has no JLC stock, so plan to consign XB3-24Z8UM modules. Mouser and DigiKey stock it.
- Blue solder mask, to match V2.

## Bench checklist

1. Before soldering to V2, meter for shorts between 3V3 and GND, and between neighbouring castellations.
2. After soldering, check each of the 12 joints for continuity to its V2 net.
3. Confirm UART traffic, CTS, SLEEP_RQ and ON/SLEEP, then reset, then join a droid's network.
4. Repeat V2's power-off test with the carrier fitted, since it adds capacitance to the rail.

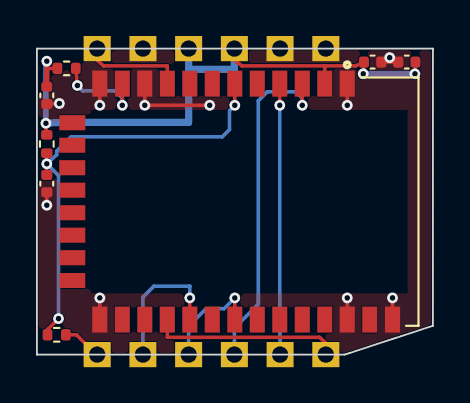
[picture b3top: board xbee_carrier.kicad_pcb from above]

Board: 2 copper layers, 22.0 x 17.0 mm, 9 parts (0 on the bottom side), 11 nets.

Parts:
C_XB_1U1: 1µF 25V X5R ±10% | CL05A105KA5NQNC | Samsung | 04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; C_0402_1005Metric
C_XB_10U1: 10µF 10V X5R ±20% | CL05A106MP5NUNC | Samsung | 0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; C_0402_1005Metric
C_XB_47P1: 47pF 50V C0G ±5% | 0402CG470J500NT | FH | 0402; C_0402_1005Metric
C_XB_RST1: 100nF 16V X7R ±10% | CL05B104KO5NNNC | Samsung | 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; C_0402_1005Metric
J_EDGE1: Castellated edge no part | Snips XBee carrier edg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; XBee_Carrier_Edge
R_XB_ATTN_PU1: 10kΩ ±1% 62.5mW | 0402WGF1002TCE | UNI-ROYAL | 04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; R_0402_1005Metric
R_XB_RST1: 100Ω ±1% 62.5mW | 0402WGF1000TCE | UNI-ROYAL | 04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; R_0402_1005Metric
R_XB_RST_PU1: 10kΩ ±1% 62.5mW | 0402WGF1002TCE | UNI-ROYAL | 04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; R_0402_1005Metric
U_XBEE1: XBee 3 PRO Zigbee 3.0 module +19dBm U.FL | XB3-24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; XB3-24Z8UM

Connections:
3V3: C_XB_1U1.1, C_XB_10U1.1, C_XB_47P1.1, J_EDGE1.9, J_EDGE1.10, R_XB_ATTN_PU1.2, R_XB_RST_PU1.2, U_XBEE1.2
/XBee/XBEE_ATTN: R_XB_ATTN_PU1.1, U_XBEE1.11
/XBee/XBEE_CTS: J_EDGE1.1, U_XBEE1.24
/XBee/XBEE_DIN: J_EDGE1.2, U_XBEE1.4
/XBee/XBEE_DOUT: J_EDGE1.3, U_XBEE1.3
/XBee/XBEE_ON_SLEEP: J_EDGE1.5, U_XBEE1.25
/XBee/XBEE_RESET: J_EDGE1.6, R_XB_RST1.1
/XBee/XBEE_RESET_RC: C_XB_RST1.1, R_XB_RST1.2, R_XB_RST_PU1.1, U_XBEE1.6
/XBee/XBEE_RTS: J_EDGE1.4, U_XBEE1.27
/XBee/XBEE_SLEEP_RQ: J_EDGE1.7, U_XBEE1.9
GND: C_XB_1U1.2, C_XB_10U1.2, C_XB_47P1.2, C_XB_RST1.2, J_EDGE1.8, J_EDGE1.11, J_EDGE1.12, U_XBEE1.1, U_XBEE1.10, U_XBEE1.12, U_XBEE1.21, U_XBEE1.32, U_XBEE1.34

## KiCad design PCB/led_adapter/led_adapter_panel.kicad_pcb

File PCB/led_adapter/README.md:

# D_RGB1 LED adapter (rev-1 boards only)

The 20 rev-1 Snips boards (10 + Alex's 10) were fabbed with the old SK6812MINI-E-012 land at
D_RGB1. That land is the datasheet's bottom view, so a lens-up LED is mirrored on it and no
rotation fixes it (see PR #65). This small adapter fixes those boards without rework. Its bottom
pads solder onto the old land, and its top carries the SK6812MINI-HS-012 land, the same footprint
the main board uses now. Boards made after PR #65 don't need it.

| Old land pad (bottom) | Net | LED pin (top) |
|---|---|---|
| 1, lower-left | GND | 1 GND |
| 2, upper-left | DIN | 2 DIN |
| 3, upper-right | 3V3 | 3 VDD |
| 4, lower-right | not connected on the main board | none (LED pin 4 DOUT is unused) |

Adapter: 6.8 x 5.6 mm, 2 layers, three 0.3 mm vias. Its outline stays clear of J_USB1, MH4,
R_RGB1/C_RGB1/R_CC2 and the board edge around D_RGB1.

## Files

- `generate_led_adapter.py` is the source. It writes `led_adapter.kicad_pcb` (one adapter) and
  `led_adapter_panel.kicad_pcb` (4 x 4 panel). Don't edit the boards by hand; change the script
  and rerun it with KiCad's Python:
  `/Applications/KiCad/KiCad.app/Contents/Frameworks/Python.framework/Versions/Current/bin/python3 PCB/led_adapter/generate_led_adapter.py`
- `production/led_adapter_panel_gerbers.zip` is the upload for the fab (Gerbers, PTH and NPTH
  Excellon drill files).

## Ordering

| Setting | Value |
|---|---|
| Layers | 2 |
| Size | 47.2 x 42.4 mm (one panel of 16 adapters) |
| Delivery format | Panel by customer, 1 design, 4 x 4, mouse-bite tabs already in the files |
| Thickness | 0.6 mm (keeps the LED low; 0.8 mm also works) |
| Surface finish | ENIG preferred (flat pads for stacking); lead-free HASL works |
| Min track / hole | 0.25 mm / 0.3 mm via, 0.5 mm NPTH (standard) |
| Quantity | The minimum (usually 5 panels = 80 adapters; at least 2 panels for the 20 boards) |

## Assembly

1. Snap the adapters out of the panel and sand the tab nubs flush on both short sides. Those
   sides sit about 0.3 mm from the USB-C connector and the mounting hole.
2. Solder the LED to the adapter top ("TOP"). The LED's chamfered corner (pin 1, GND) goes to the
   corner with the ▲ mark, on the side away from "USB".
3. Tin the old D_RGB1 pads and the adapter's bottom pads lightly. Place the adapter with the
   arrow pointing at the USB-C connector. The pad marked "NC" on the bottom goes over the
   main-board pad with no trace running to it. Reflow with hot air or a hotplate.
4. Before powering the board, check that 3V3 is not shorted to GND. Then check that the LED lights.

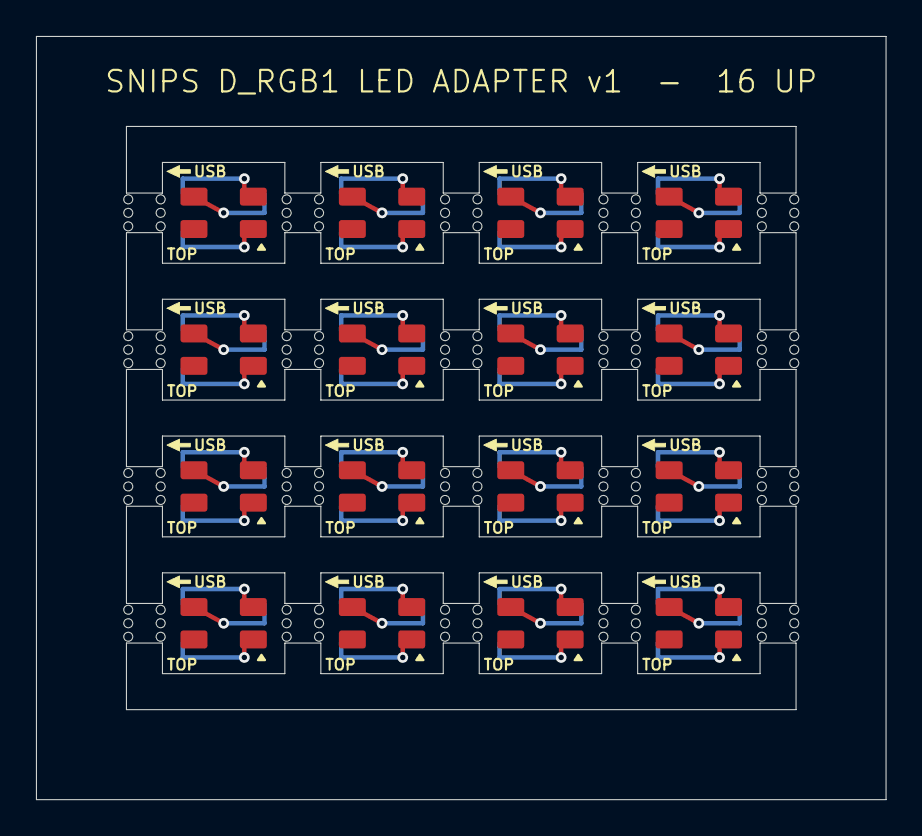
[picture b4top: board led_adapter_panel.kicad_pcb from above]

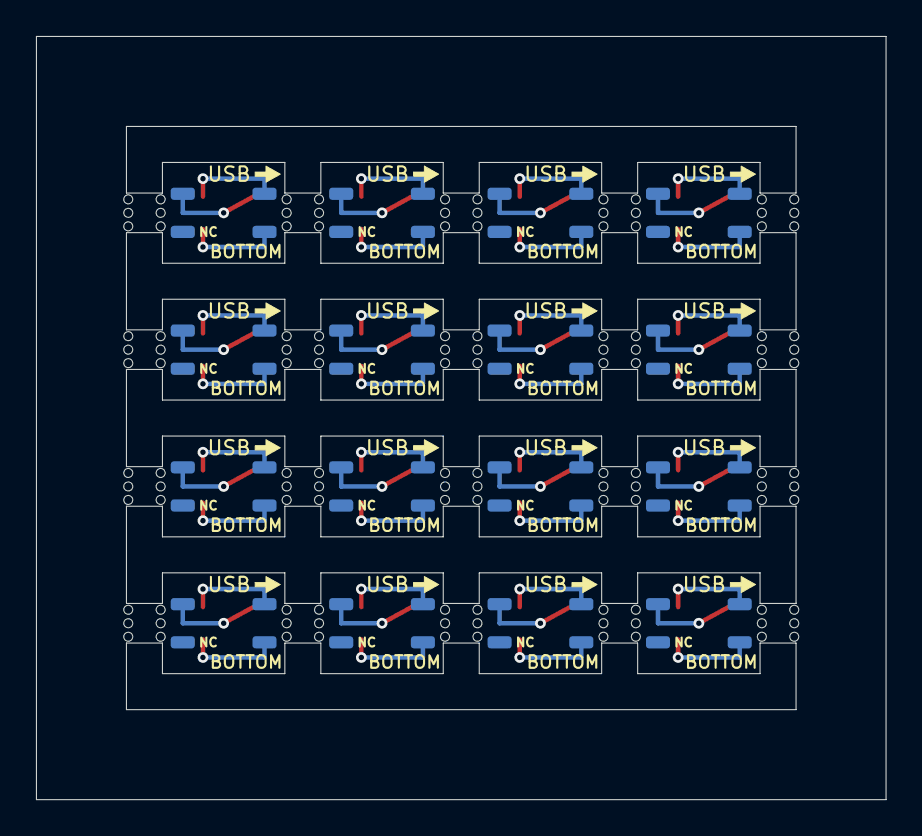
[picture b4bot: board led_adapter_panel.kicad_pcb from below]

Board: 2 copper layers, 47.2 x 42.4 mm, 33 parts (16 on the bottom side), 48 nets.

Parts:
D1, D2, D3, D4, D5, D6, D7, D8, D9, D10, D11, D12, D13, D14, D15, D16: SK6812MINI-HS-012
J1, J2, J3, J4, J5, J6, J7, J8, J9, J10, J11, J12, J13, J14, J15, J16: SK6812MINI-E-012_mate
MB1: MouseBites

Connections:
/A1/3V3: D1.3, J1.3
/A1/DIN: D1.2, J1.2
/A1/GND: D1.1, J1.1
/A2/3V3: D2.3, J2.3
/A2/DIN: D2.2, J2.2
/A2/GND: D2.1, J2.1
/A3/3V3: D3.3, J3.3
/A3/DIN: D3.2, J3.2
/A3/GND: D3.1, J3.1
/A4/3V3: D4.3, J4.3
/A4/DIN: D4.2, J4.2
/A4/GND: D4.1, J4.1
/A5/3V3: D5.3, J5.3
/A5/DIN: D5.2, J5.2
/A5/GND: D5.1, J5.1
/A6/3V3: D6.3, J6.3
/A6/DIN: D6.2, J6.2
/A6/GND: D6.1, J6.1
/A7/3V3: D7.3, J7.3
/A7/DIN: D7.2, J7.2
/A7/GND: D7.1, J7.1
/A8/3V3: D8.3, J8.3
/A8/DIN: D8.2, J8.2
/A8/GND: D8.1, J8.1
/A9/3V3: D9.3, J9.3
/A9/DIN: D9.2, J9.2
/A9/GND: D9.1, J9.1
/A10/3V3: D10.3, J10.3
/A10/DIN: D10.2, J10.2
/A10/GND: D10.1, J10.1
/A11/3V3: D11.3, J11.3
/A11/DIN: D11.2, J11.2
/A11/GND: D11.1, J11.1
/A12/3V3: D12.3, J12.3
/A12/DIN: D12.2, J12.2
/A12/GND: D12.1, J12.1
/A13/3V3: D13.3, J13.3
/A13/DIN: D13.2, J13.2
/A13/GND: D13.1, J13.1
/A14/3V3: D14.3, J14.3
/A14/DIN: D14.2, J14.2
/A14/GND: D14.1, J14.1
/A15/3V3: D15.3, J15.3
/A15/DIN: D15.2, J15.2
/A15/GND: D15.1, J15.1
/A16/3V3: D16.3, J16.3
/A16/DIN: D16.2, J16.2
/A16/GND: D16.1, J16.1
